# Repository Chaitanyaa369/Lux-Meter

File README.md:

💡 Lux Meter with ESP8266

This project is a web-based Lux Meter built using an ESP8266 microcontroller. It measures light intensity using a light sensor and displays the data graphically in real-time through a web interface. The design includes firmware, HTML/JS/CSS for visualization, and a custom-designed PCB.

📦 Project Structure

    Lux-Meter/
    │
    ├── Lux_meter/
    |    ├── Lux_meter.ino             # Firmware for ESP8266
    |    ├── index.html                # Web interface to visualize Lux data
    |    ├── style.css                 # Styling for the web interface
    │
    ├── Lux_Meter.sch             # Schematic file (Eagle)
    ├── Lux_Meter.brd             # PCB layout file (Eagle)
    ├── LM-Top.pdf                # PCB top view
    ├── LM-Bottom.pdf             # PCB bottom view
    ├── LM-C_name_value.pdf       # Component name/value placement
    ├── LM -components.pdf        # Components and connections
    │
    └── README.md                 # This file

🧠 Features

- Real-time Lux data visualization using Highcharts

- Simple Start/Stop/Reset buttons for live data streaming

- ESP8266-hosted web server

- Minimal and responsive interface

- Custom PCB design for compact integration

🔧 Hardware Used

- ESP8266 (ESP-12E/F)

- Light sensor (LDR or BH1750)

- LM1117-3.3V voltage regulator

- Capacitors: 100nF, 470pF, 47uF

- Resistors: 12K

- USB-to-Serial interface

- Misc: Connectors, header pins

You can view the hardware setup using:

- 📄 LM -components.pdf

- 🖼️ LM-Top.pdf and LM-Bottom.pdf

- 📐 LM-C_name_value.pdf

💻 Software Used

- Arduino IDE (for programming ESP8266)

- EAGLE CAD (for PCB design)

- HTML/CSS/JavaScript + Highcharts.js (for plotting)

🚀 Getting Started
Flash the Firmware:

1. Open Lux_meter.ino in Arduino IDE.

2. Install the ESP8266 board support (via Boards Manager).

3. Upload the sketch to the ESP8266.

Web Interface:

The ESP8266 serves the index.html and style.css from flash or SPIFFS.

- Open a browser to the ESP8266's IP address.

- The interface provides:

    - 📈 Real-time chart

    - ▶️ Start streaming

    - ⏹️ Stop streaming

    - 🔄 Reset the chart

PCB:

1. Open Lux_Meter.sch and Lux_Meter.brd in EAGLE.

2. Use the provided PDFs for a quick view of the design and component placement.

🌐 How It Works

- The ESP8266 reads Lux values periodically from the sensor.

- A lightweight web server handles HTTP requests to fetch data.

- The web interface uses JavaScript + Highcharts to plot values dynamically.

📄 License

MIT License. Portions of the web UI adapted from RandomNerdTutorials.
🙏 Acknowledgments

- Rui Santos (Random Nerd Tutorials) for the ESP8266 web interface inspiration

- Highcharts.js for charting library

- Eagle CAD for PCB design

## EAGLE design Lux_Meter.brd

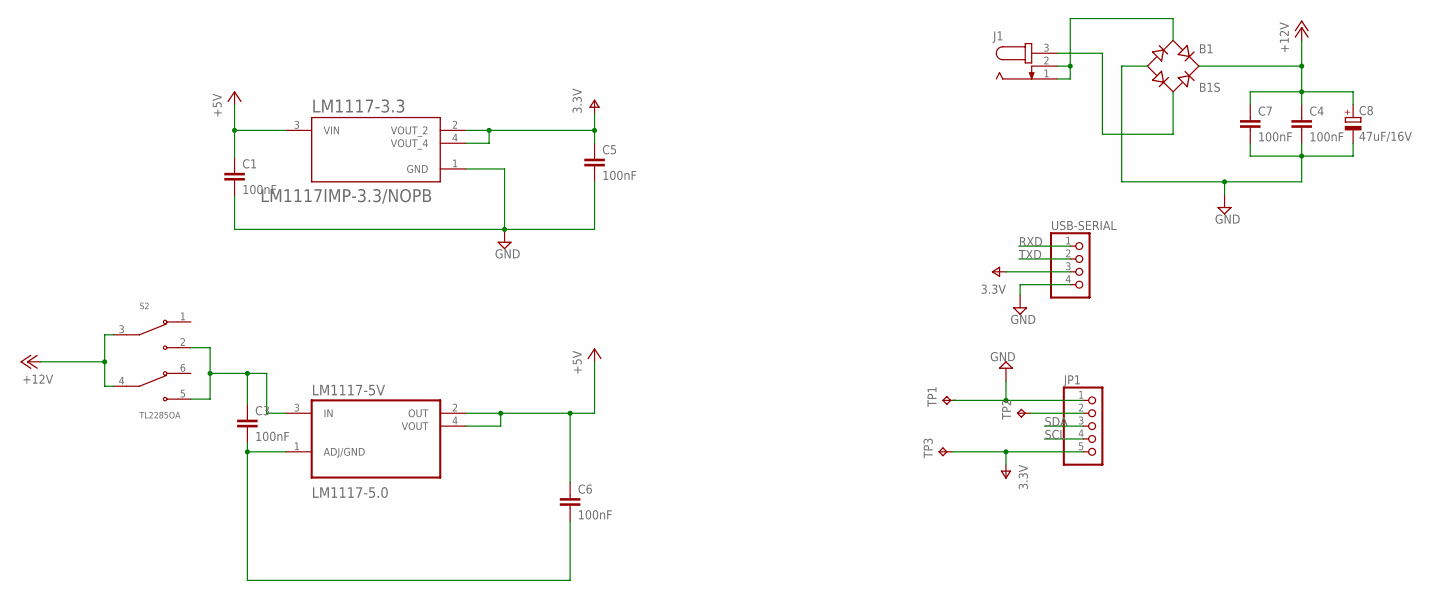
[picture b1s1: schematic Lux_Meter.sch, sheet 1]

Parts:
B1: B1S; MBS
C1, C3, C4: 100nF; C0603K
C5, C6, C7: 100nF; C0805K
C8: 47uF/16V; C/6032-28R
J1: JACK-PLUG0; SPC4077
JP1: PINHD-1X5; 1X05
LM1117-3.3: LM1117IMP-3.3/NOPB; VREG_LM1117IMP-3.3/NOPB
LM1117-5V: LM1117-5.0; SOT230P700X180-4N
S2: TL2285OA; SW_TL2285OA
TP1, TP2, TP3: TPTP13SQ; TP13SQ
USB-SERIAL: PINHD-1X4; 1X04

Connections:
+5V: C1.1, C6.1, LM1117-3.3.3 (VIN), LM1117-5V.2 (OUT), LM1117-5V.4 (VOUT)
+12V: B1.+, C4.1, C7.1, C8.+, S2.3 (COM1), S2.4 (COM2)
GND: B1.-, C1.2, C4.2, C5.2, C7.2, C8.-, JP1.1, LM1117-3.3.1 (GND), TP1.TP, USB-SERIAL.4; also elsewhere on the board
unnamed: B1.AC1, J1.1, J1.2
unnamed: B1.AC2, J1.3
unnamed: JP1.2, TP2.TP
unnamed: C3.2, C6.2, LM1117-5V.1 (ADJ/GND)
unnamed: C3.1, LM1117-5V.3 (IN), S2.2 (NO1), S2.5 (NO2)
RXD: USB-SERIAL.1; also elsewhere on the board
SCL: JP1.4; also elsewhere on the board
SDA: JP1.3; also elsewhere on the board
TXD: USB-SERIAL.2; also elsewhere on the board
V+: C5.1, JP1.5, LM1117-3.3.2 (VOUT_2), LM1117-3.3.4 (VOUT_4), TP3.TP, USB-SERIAL.3; also elsewhere on the board

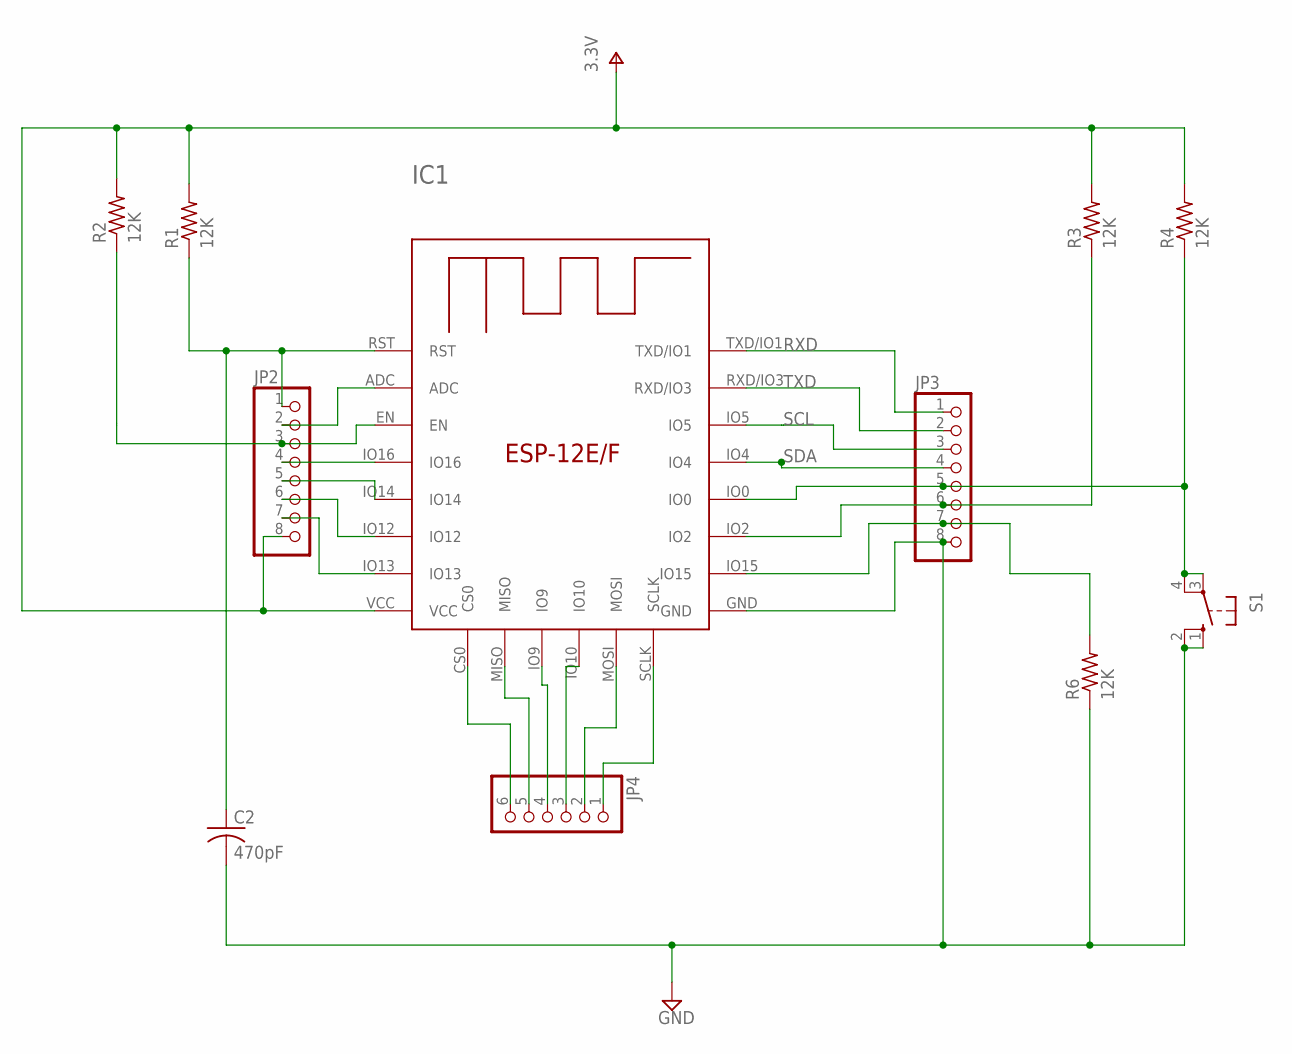
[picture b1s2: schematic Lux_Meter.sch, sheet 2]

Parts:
C2: 470pF; C0805
IC1: ESP-12E/F; ESP-12E
JP2, JP3: PINHD-1X8; 1X08
JP4: PINHD-1X6; 1X06
R1, R2, R3, R4, R6: 12K; R0805
S1: 10-XX; B3F-10XX

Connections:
GND: C2.2, IC1.GND, JP3.8, R6.1, S1.1 (S), S1.2 (S1); also elsewhere on the board
unnamed: C2.1, IC1.RST, JP2.1, R1.1
unnamed: IC1.IO15, JP3.7, R6.2
unnamed: IC1.IO0, JP3.5, R4.1, S1.3, S1.4 (P1)
unnamed: IC1.SCLK, JP4.1
unnamed: IC1.IO2, JP3.6, R3.1
unnamed: IC1.ADC, JP2.2
unnamed: IC1.EN, JP2.3, R2.1
unnamed: IC1.IO16, JP2.4
unnamed: IC1.IO14, JP2.5
unnamed: IC1.IO12, JP2.6
unnamed: IC1.IO13, JP2.7
unnamed: IC1.MOSI, JP4.2
unnamed: IC1.IO10, JP4.3
unnamed: IC1.IO9, JP4.4
unnamed: IC1.MISO, JP4.5
unnamed: IC1.CS0, JP4.6
RXD: IC1.TXD/IO1, JP3.1; also elsewhere on the board
SCL: IC1.IO5, JP3.3; also elsewhere on the board
SDA: IC1.IO4, JP3.4; also elsewhere on the board
TXD: IC1.RXD/IO3, JP3.2; also elsewhere on the board
V+: IC1.VCC, JP2.8, R1.2, R2.2, R3.2, R4.2; also elsewhere on the board

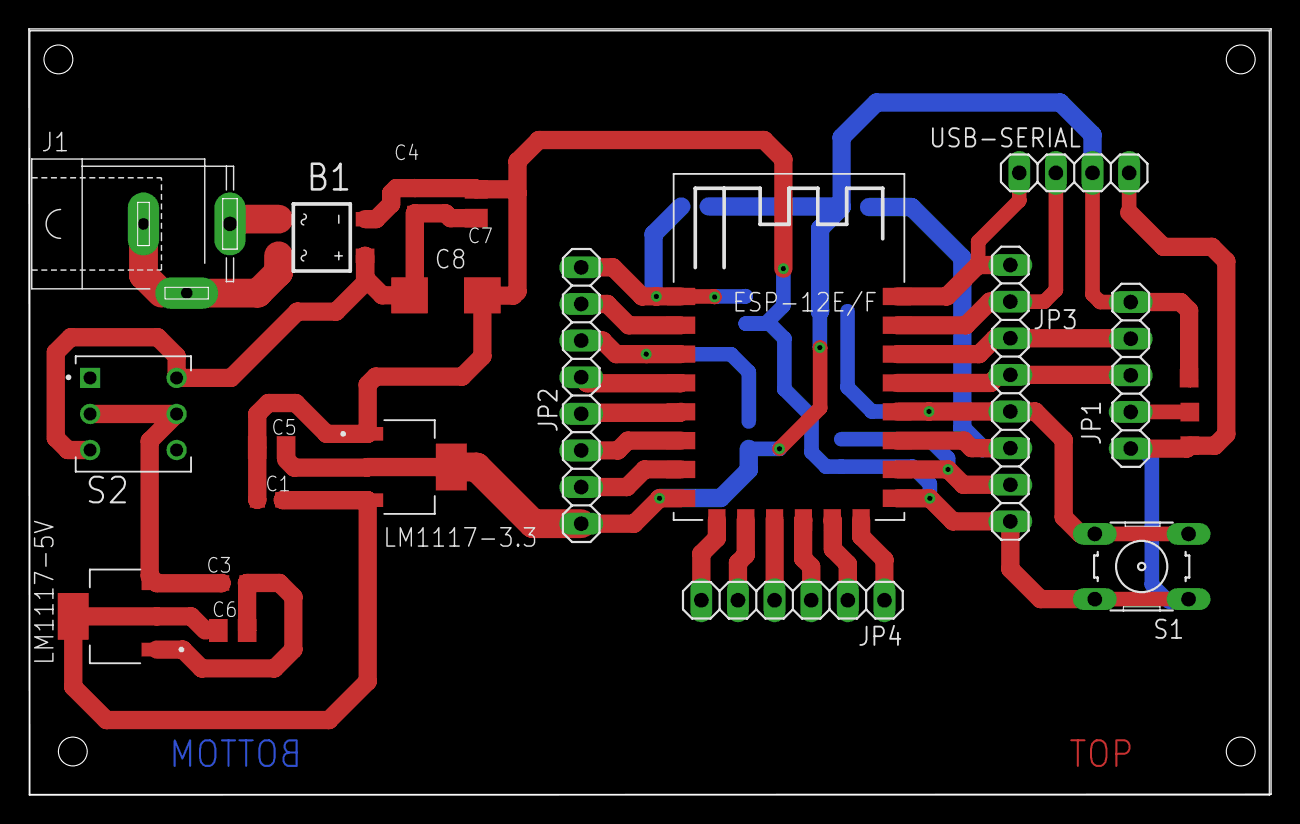
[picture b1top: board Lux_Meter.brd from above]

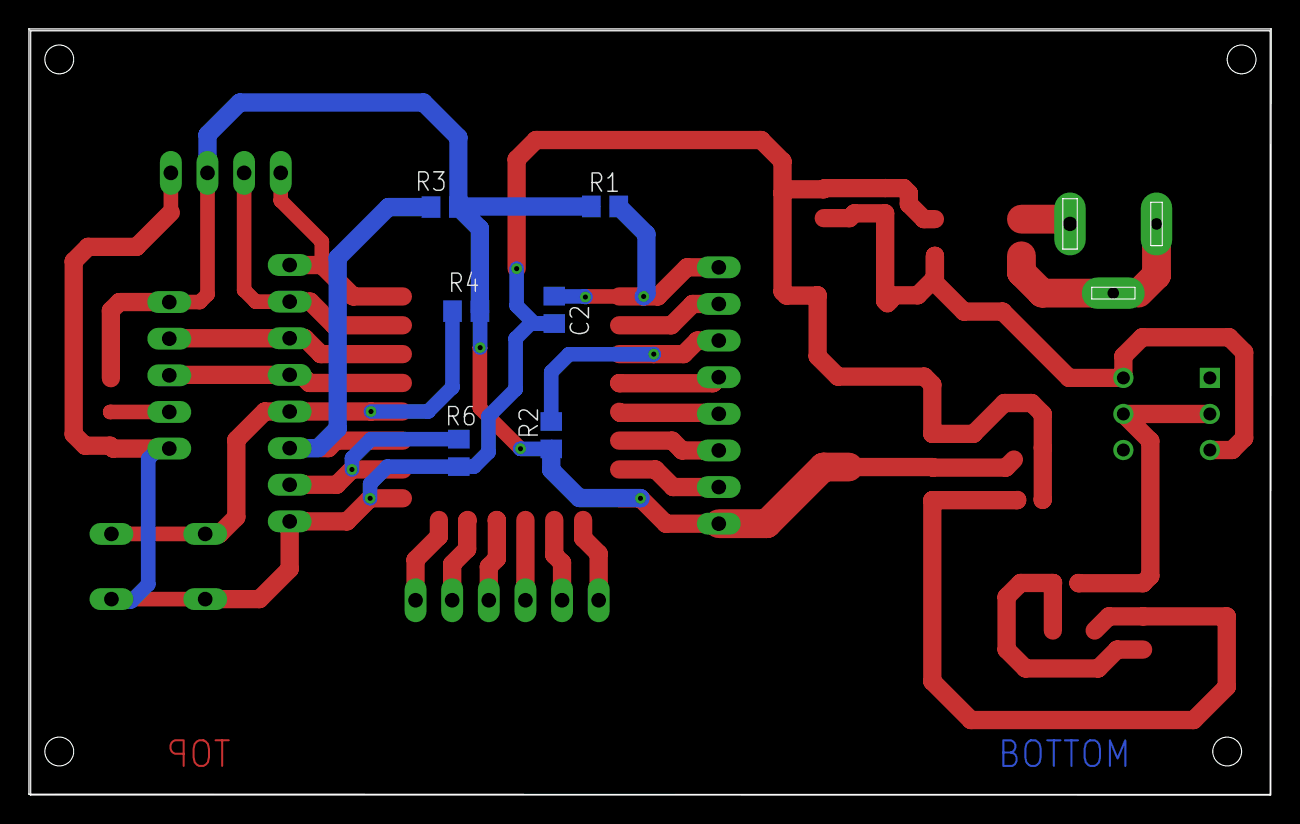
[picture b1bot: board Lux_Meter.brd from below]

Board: 2 copper layers, 86.2 x 53.1 mm, 28 parts (6 on the bottom side), 29 nets.

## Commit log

2022-10-16 initial commit; sch,brd and ino
2022-10-26 Add files via upload
    PDF files of the layout.
2022-12-09 added calibration and start, stop, reset
